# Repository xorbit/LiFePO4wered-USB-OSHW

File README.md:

# LiFePO4wered-USB-OSHW

This repository contains the design files for the [LiFePO4wered/USB](http://lifepo4wered.com) power module.
Updated to the latest revision 3.

The files are created in [Cadsoft Eagle](http://www.cadsoftusa.com/eagle-pcb-design-software/).

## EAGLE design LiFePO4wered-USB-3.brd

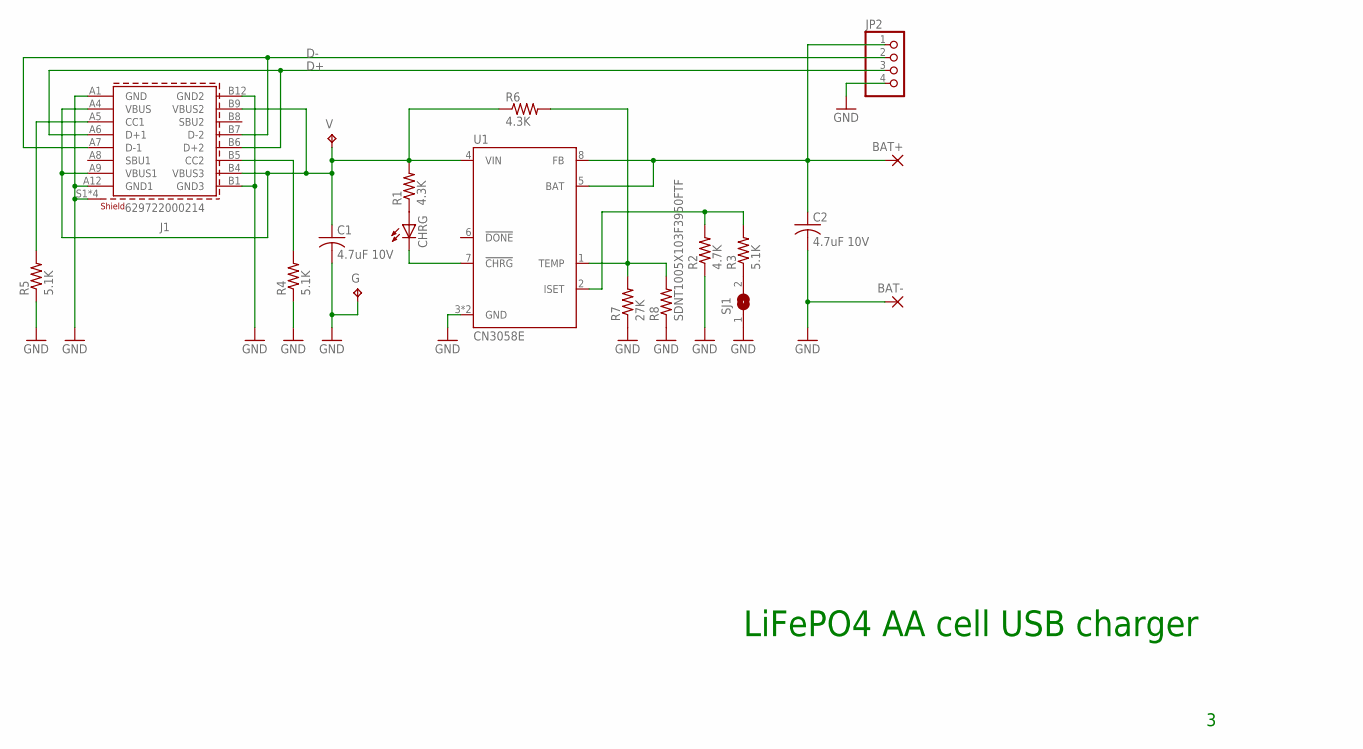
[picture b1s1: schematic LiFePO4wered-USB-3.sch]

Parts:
BAT+: 2,54/1,0
BAT-: 2,54/1,0
C1, C2: 4.7uF 10V; C0603
CHRG: LEDCHIP-LED0603; CHIP-LED0603
G: TPTP20R; TP20R
J1: 629722000214
JP2: PINHD-1X4; 1X04
R1, R6: 4.3K; R0402
R2: 4.7K; R0402
R3, R4, R5: 5.1K; R0402
R7: 27K; R0402
R8: SDNT1005X103F3950FTF; R0402
SJ1: SJ
U1: CN3058E; SO08-THERMAL
V: TPTP20R; TP20R

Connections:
D+: J1.A6 (D+1), J1.B6 (D+2), JP2.3
D-: J1.A7 (D-1), J1.B7 (D-2), JP2.2
GND: BAT-.1, C1.2, C2.2, G.TP, J1.A1 (GND), J1.A12 (GND1), J1.B1 (GND3), J1.B12 (GND2), J1.S1 (SHIELD), J1.S2 (SHIELD), J1.S3 (SHIELD), J1.S4 (SHIELD), JP2.4, R2.1, R4.1, R5.1, R7.1, R8.1, SJ1.1, U1.3 (GND), U1.PAD (GND)
unnamed: C1.1, J1.A4 (VBUS), J1.A9 (VBUS1), J1.B4 (VBUS3), J1.B9 (VBUS2), R1.2, R6.1, U1.4 (VIN), V.TP
unnamed: CHRG.A, R1.1
unnamed: CHRG.C, U1.7 (!CHRG)
unnamed: R6.2, R7.2, R8.2, U1.1 (TEMP)
unnamed: BAT+.1, C2.1, JP2.1, U1.5 (BAT), U1.8 (FB)
unnamed: R2.2, R3.2, U1.2 (ISET)
unnamed: J1.A5 (CC1), R5.2
unnamed: J1.B5 (CC2), R4.2
unnamed: R3.1, SJ1.2

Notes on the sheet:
LiFePO4 AA cell USB charger

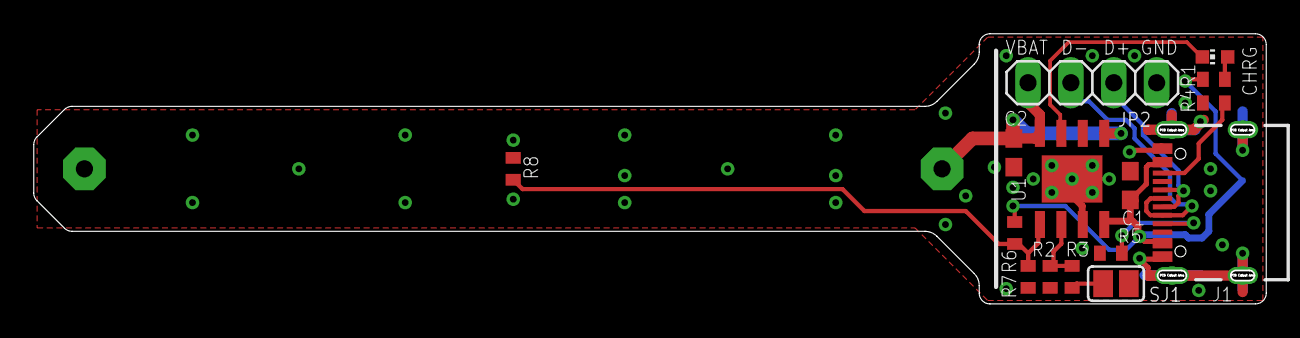
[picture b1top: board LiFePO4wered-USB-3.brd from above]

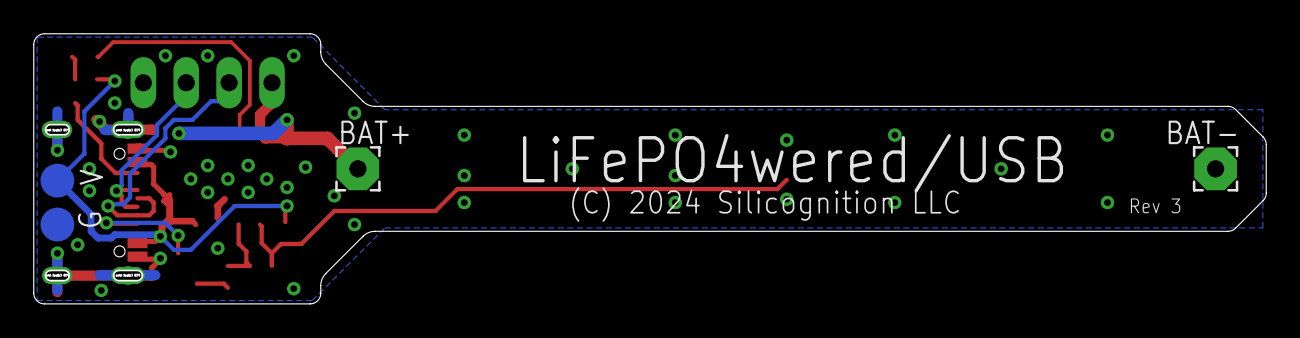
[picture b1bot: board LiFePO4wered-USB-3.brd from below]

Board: 2 copper layers, 72.9 x 15.9 mm, 19 parts (4 on the bottom side), 12 nets.

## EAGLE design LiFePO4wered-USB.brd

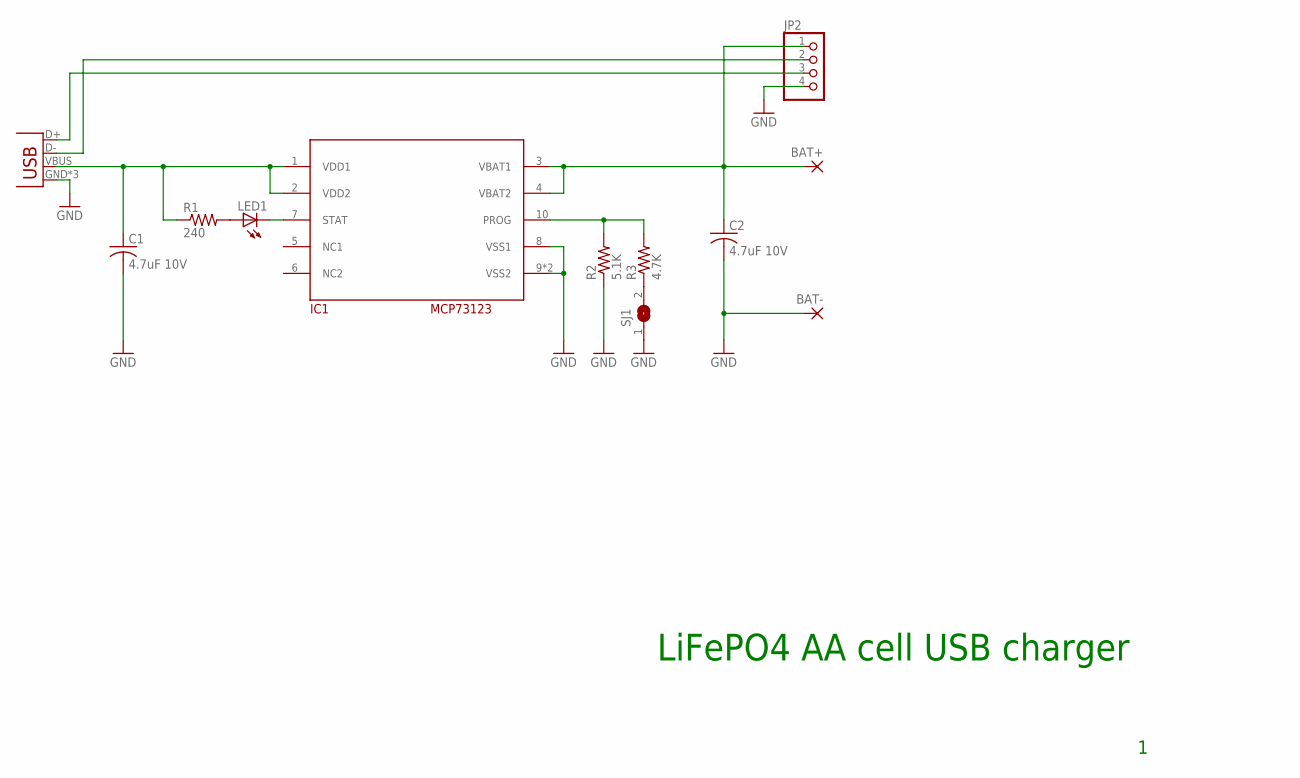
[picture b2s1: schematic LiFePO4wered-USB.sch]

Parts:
BAT+: 2,54/1,0
BAT-: 2,54/1,0
C1, C2: 4.7uF 10V; C0603
IC1: MCP73123; DFN10-3X3
JP1: USB-MICROB
JP2: PINHD-1X4; 1X04
LED1: LEDCHIP-LED0603; CHIP-LED0603
R1: 240; R0603
R2: 5.1K; R0603
R3: 4.7K; R0603
SJ1: SJ

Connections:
GND: BAT-.1, C1.2, C2.2, IC1.8 (VSS1), IC1.9 (VSS2), IC1.EXP (VSS2), JP1.GND, JP1.MT1 (GND), JP1.MT2 (GND), JP2.4, R2.1, SJ1.1
unnamed: C1.1, IC1.1 (VDD1), IC1.2 (VDD2), JP1.VBUS, R1.1
unnamed: LED1.A, R1.2
unnamed: IC1.7 (STAT), LED1.C
unnamed: R3.1, SJ1.2
unnamed: BAT+.1, C2.1, IC1.3 (VBAT1), IC1.4 (VBAT2), JP2.1
unnamed: IC1.10 (PROG), R2.2, R3.2
unnamed: JP1.D-, JP2.2
unnamed: JP1.D+, JP2.3

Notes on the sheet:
LiFePO4 AA cell USB charger

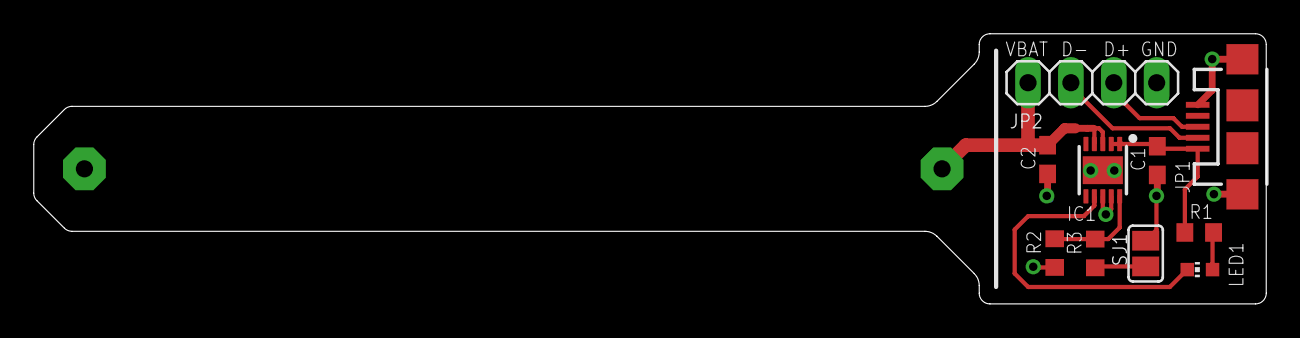
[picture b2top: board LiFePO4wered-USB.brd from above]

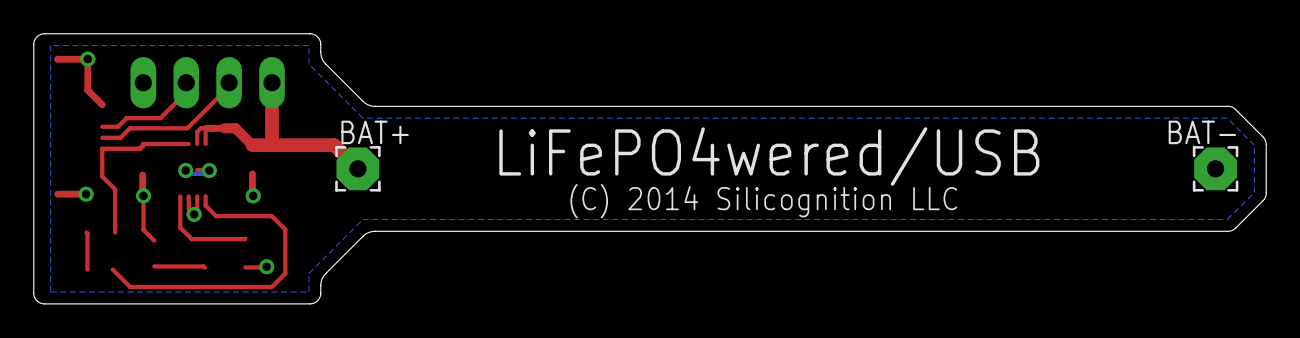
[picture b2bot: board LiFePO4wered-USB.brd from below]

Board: 2 copper layers, 73.0 x 16.0 mm, 12 parts (2 on the bottom side), 9 nets.

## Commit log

2015-08-17 Initial commit as Open Source Hardware
2015-09-16 Add schematic PDF
2025-04-28 Updated to newest revision 3.

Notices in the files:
LiFePO4wered-USB-3.brd:
(C) 2024 Silicognition LLC
LiFePO4wered-USB.brd:
(C) 2014 Silicognition LLC
parts and their libraries:
Eagle_WR-USB-rev22c: Copyright: Würth Elektronik
SparkFun-Connectors: Licensing: Creative Commons ShareAlike 4.0 International - https://creativecommons.org/licenses/by-sa/4.0
